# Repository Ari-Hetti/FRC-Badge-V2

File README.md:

# FRC Badge V2
A small keychain pcb in the shape of a hexagon that lights up LEDs using a 555 chase circuit and is powered by usb-c

I built this project because I want to integrate my electronic skills with a major part of my life - FRC. I also wanted a cool keychain to have and thought might as well build it myself

The main use case for this project is to connect to backpack using the hole in the top. If I want to power it I can just plug into any usb-c leaving me an easy way to power it on the go

This is V2 redesign from my first design which was built as part of Hackclub Solder. [FRC_Badge V1](https://github.com/Ari-Hetti/FRC_Badge)

Built with help from Hackclub Blueprint

# Contact
@Ari H. U08QRTADZTJ

# Pictures
| Schematic | PCB | 3D Front | 3D Back | 
|------------------|--------------------|-------------|-------|
| |  |  | |

# BOM

| Component | QTY | 
|----------|--------|
| NE555P | 1 |
| CD4017 | 1 |
| 1uF Elctrolytic Capacitor | 1 |
| 0.01uF Capacitor | 1 |
| Potentiometer | 1 |
| 1K Ohm Resitor | 1 |
| 470 Ohm Resistor | 1 |
| 5k Ohm Resistor | 2 |
| LEDs | 10 |
| 1x1 Female Connector| 1 |
| 6p Power USB-C connector | 1 |

## Tools

This project uses:

- [KiCad](https://www.kicad.org/)
- [Hack Club Blueprint Blinky Tutorial](https://blueprint.hackclub.com/starter-projects/blinky)

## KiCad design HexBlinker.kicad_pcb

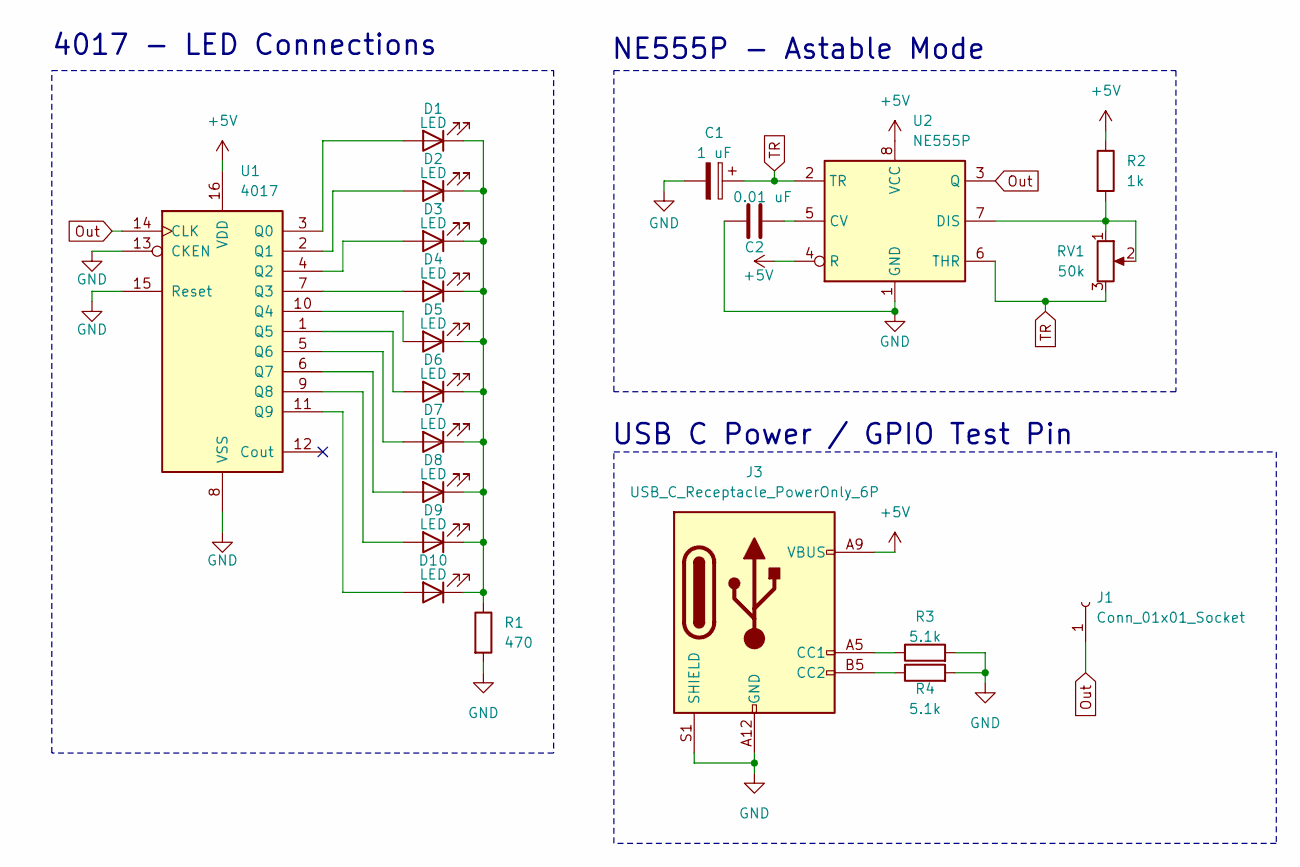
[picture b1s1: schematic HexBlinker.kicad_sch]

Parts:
C1: 1 uF; CP_Radial_D5.0mm_P2.00mm
C2: 0.01 uF; C_Disc_D7.5mm_W2.5mm_P5.00mm
D1, D2, D3, D4, D5, D6, D7, D8, D9, D10: LED; LED_D3.0mm
J1: Conn_01x01_Socket; PinSocket_1x01_P2.54mm_Vertical
J3: USB_C_Receptacle_PowerOnly_6P; USB_C_Receptacle_GCT_USB4125-xx-x_6P_TopMnt_Horizontal
R1: 470; R_Axial_DIN0207_L6.3mm_D2.5mm_P7.62mm_Horizontal
R2: 1k; R_Axial_DIN0207_L6.3mm_D2.5mm_P7.62mm_Horizontal
R3, R4: 5.1k; R_Axial_DIN0207_L6.3mm_D2.5mm_P7.62mm_Horizontal
RV1: 50k; Potentiometer_Vishay_T93YA_Vertical
U1: 4017; N16
U2: NE555P; DIP-8_W7.62mm

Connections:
+5V: J3.A9 (VBUS), J3.B9 (VBUS), R2.1, U1.16 (VDD), U2.4 (R), U2.8 (VCC)
GND: C1.2, C2.1, J3.A12 (GND), J3.B12 (GND), J3.S1 (SHIELD), R1.2, R3.2, R4.2, U1.8 (VSS), U1.13 (CKEN), U1.15 (Reset), U2.1 (GND)
unnamed: D1.2 (A), U1.3 (Q0)
unnamed: D1.1 (K), D2.1 (K), D3.1 (K), D4.1 (K), D5.1 (K), D6.1 (K), D7.1 (K), D8.1 (K), D9.1 (K), D10.1 (K), R1.1
unnamed: D2.2 (A), U1.2 (Q1)
unnamed: D3.2 (A), U1.4 (Q2)
unnamed: D4.2 (A), U1.7 (Q3)
unnamed: D5.2 (A), U1.10 (Q4)
unnamed: D6.2 (A), U1.1 (Q5)
unnamed: D7.2 (A), U1.5 (Q6)
unnamed: D8.2 (A), U1.6 (Q7)
unnamed: D9.2 (A), U1.9 (Q8)
unnamed: D10.2 (A), U1.11 (Q9)
unnamed: J3.A5 (CC1), R3.1
unnamed: J3.B5 (CC2), R4.1
unnamed: C2.2, U2.5 (CV)
unnamed: R2.2, RV1.1, RV1.2, U2.7 (DIS)
Out: J1.1, U1.14 (CLK), U2.3 (Q)
TR: C1.1, RV1.3, U2.2 (TR), U2.6 (THR)

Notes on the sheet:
NE555P - Astable Mode
4017 - LED Connections
USB C Power / GPIO Test Pin

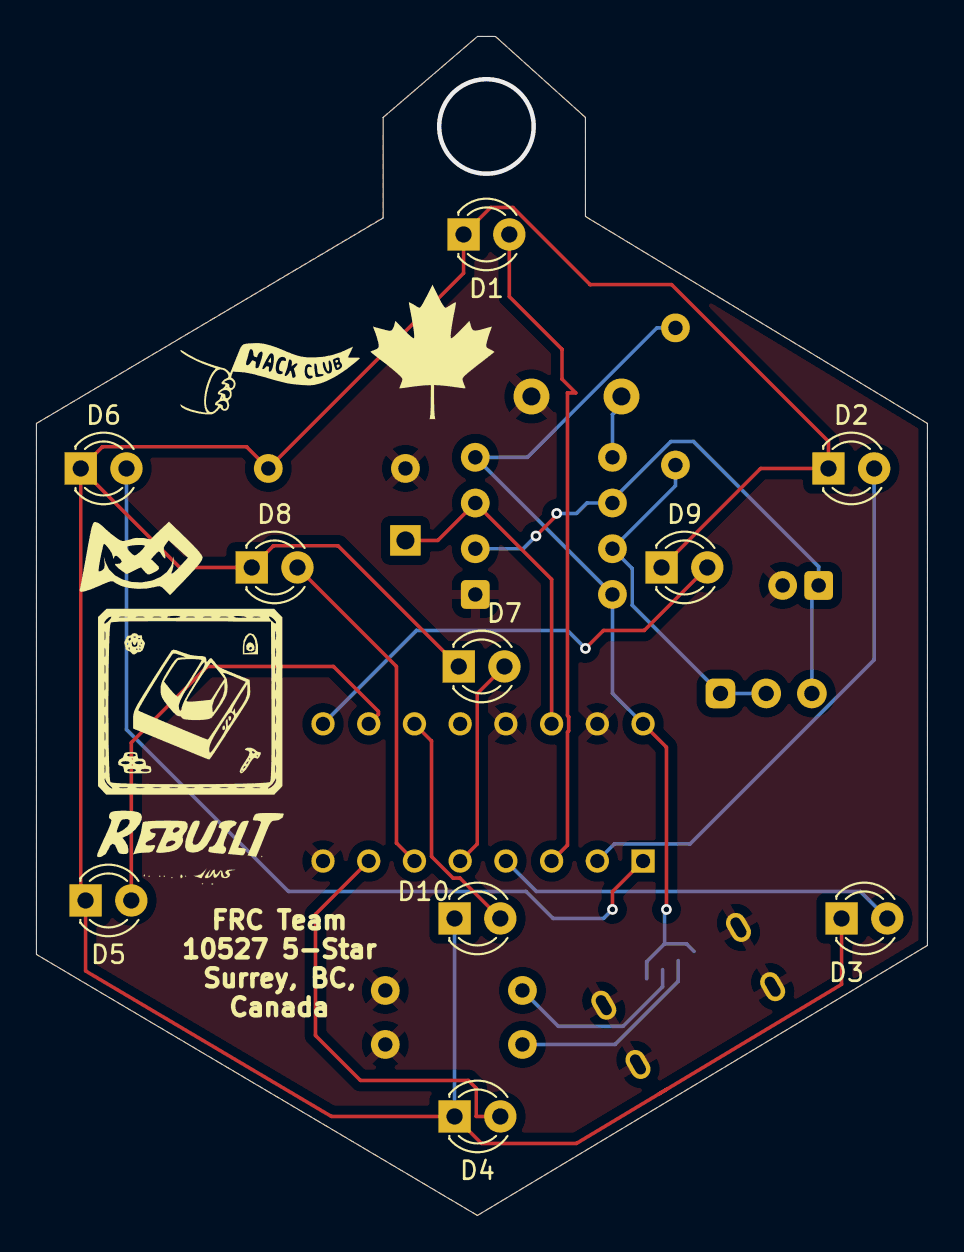
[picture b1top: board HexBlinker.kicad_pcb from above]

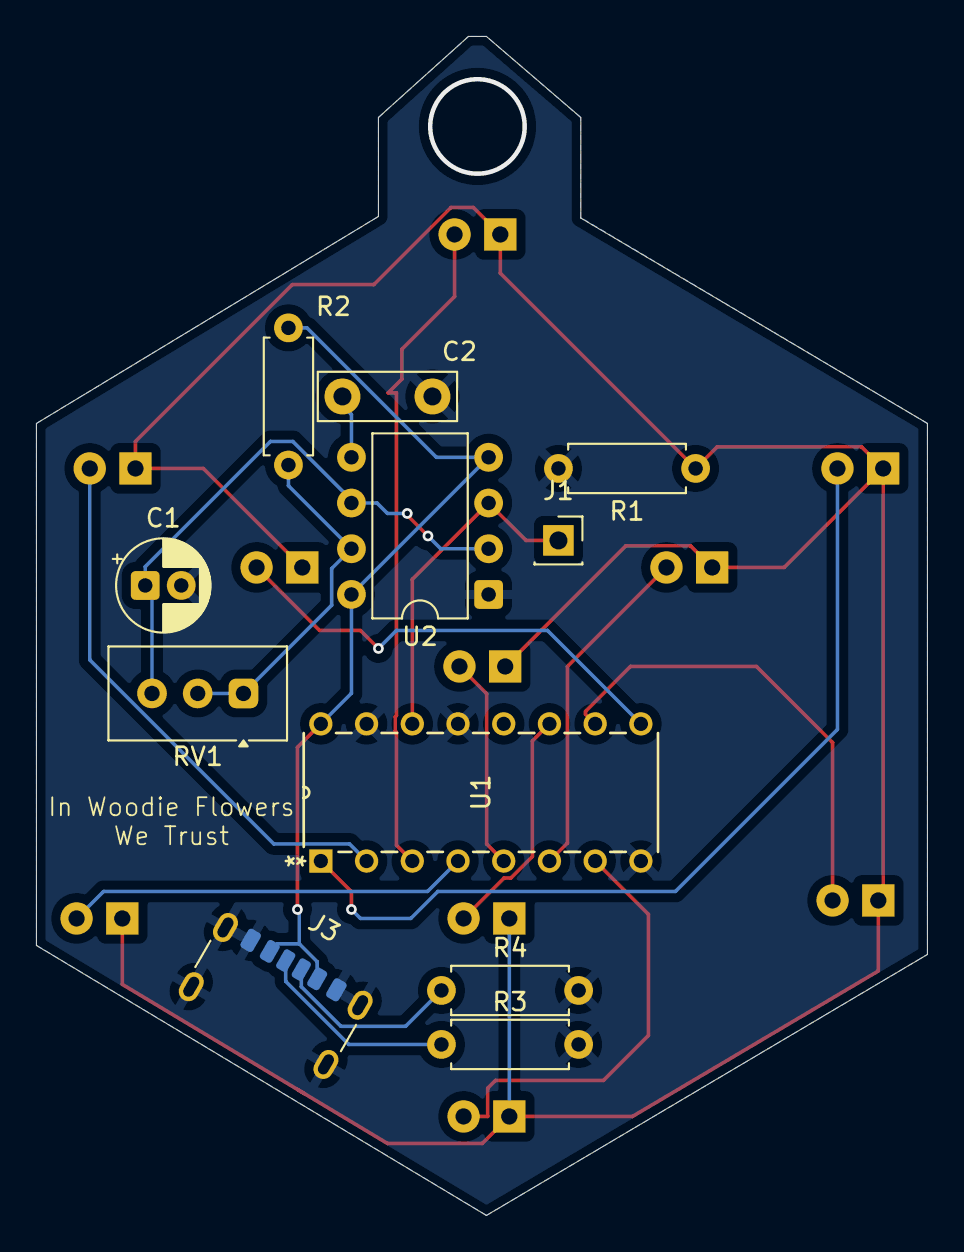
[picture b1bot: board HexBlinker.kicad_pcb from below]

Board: 2 copper layers, 49.5 x 65.5 mm, 21 parts (11 on the bottom side), 19 nets.

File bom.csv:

Designator,Footprint,Quantity,Value,LCSC Part #
C1,CP_Radial_D5.0mm_P2.00mm,1,1 uF,
C2,C_Disc_D7.5mm_W2.5mm_P5.00mm,1,0.01 uF,
"D1, D10, D2, D3, D4, D5, D6, D7, D8, D9",LED_D3.0mm,10,LED,
J1,PinSocket_1x01_P2.54mm_Vertical,1,Conn_01x01_Socket,
J3,USB_C_Receptacle_GCT_USB4125-xx-x_6P_TopMnt_Horizontal,1,USB_C_Receptacle_PowerOnly_6P,
R1,R_Axial_DIN0207_L6.3mm_D2.5mm_P7.62mm_Horizontal,1,470,
R2,R_Axial_DIN0207_L6.3mm_D2.5mm_P7.62mm_Horizontal,1,1k,
"R3, R4",R_Axial_DIN0207_L6.3mm_D2.5mm_P7.62mm_Horizontal,2,5.1k,
RV1,Potentiometer_Vishay_T93YA_Vertical,1,50k,
U1,N16,1,4017,
U2,DIP-8_W7.62mm,1,NE555P,

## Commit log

2026-02-04 Fix typo in README description
2026-02-15 Rename FRC Badge V2 Schematic.png to Images/FRC Badge V2 Schematic.png
2026-02-15 Rename FRC Badge V2 Back 3d.png to Images/FRC Badge V2 Back 3d.png
2026-02-15 Rename FRC Badge V2 Front 3d.png to Images /FRC Badge V2 Front 3d.png
2026-02-15 Rename FRC Badge V2 Front 3d.png to FRC Badge V2 Front 3d.png
2026-02-15 Rename FRC Badge V2 PCB.png to Images/FRC Badge V2 PCB.png
2026-02-15 Rename HexBlinker.kicad_prl to PCB/HexBlinker.kicad_prl
2026-02-15 Rename HexBlinker.kicad_pro to PCB/HexBlinker.kicad_pro
2026-02-15 Rename HexBlinker.zip to production/HexBlinker.zip
2026-02-15 Enhance README with project details and contact info
    Expanded project description and added contact information.
2026-02-15 Add pictures section to README
    Added a section for pictures with schematic, PCB, and 3D views.
2026-02-15 Rename HexBlinker.step to CAD/HexBlinker.step
2026-02-15 Update README with project details and context
    Added project motivation, use case, and redesign information.
2026-02-15 Add BOM section to README
    Added Bill of Materials (BOM) section with components and quantities.
2026-02-15 Update README with tools and project link
    Added project tools and updated project description with a link.
2026-03-20 Update to PCB before manufacturing.
    I changed to pcb to reflect our new robot name and the Gracious Professionalism award we won at CANPAC 2026
2026-03-20 Update PCB image and dimensions in README
